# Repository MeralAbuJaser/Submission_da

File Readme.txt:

Student Name: Meral Abu-Jaser

Student #: 5003137888

Student Email: abujaser@unlv.nevada.edu

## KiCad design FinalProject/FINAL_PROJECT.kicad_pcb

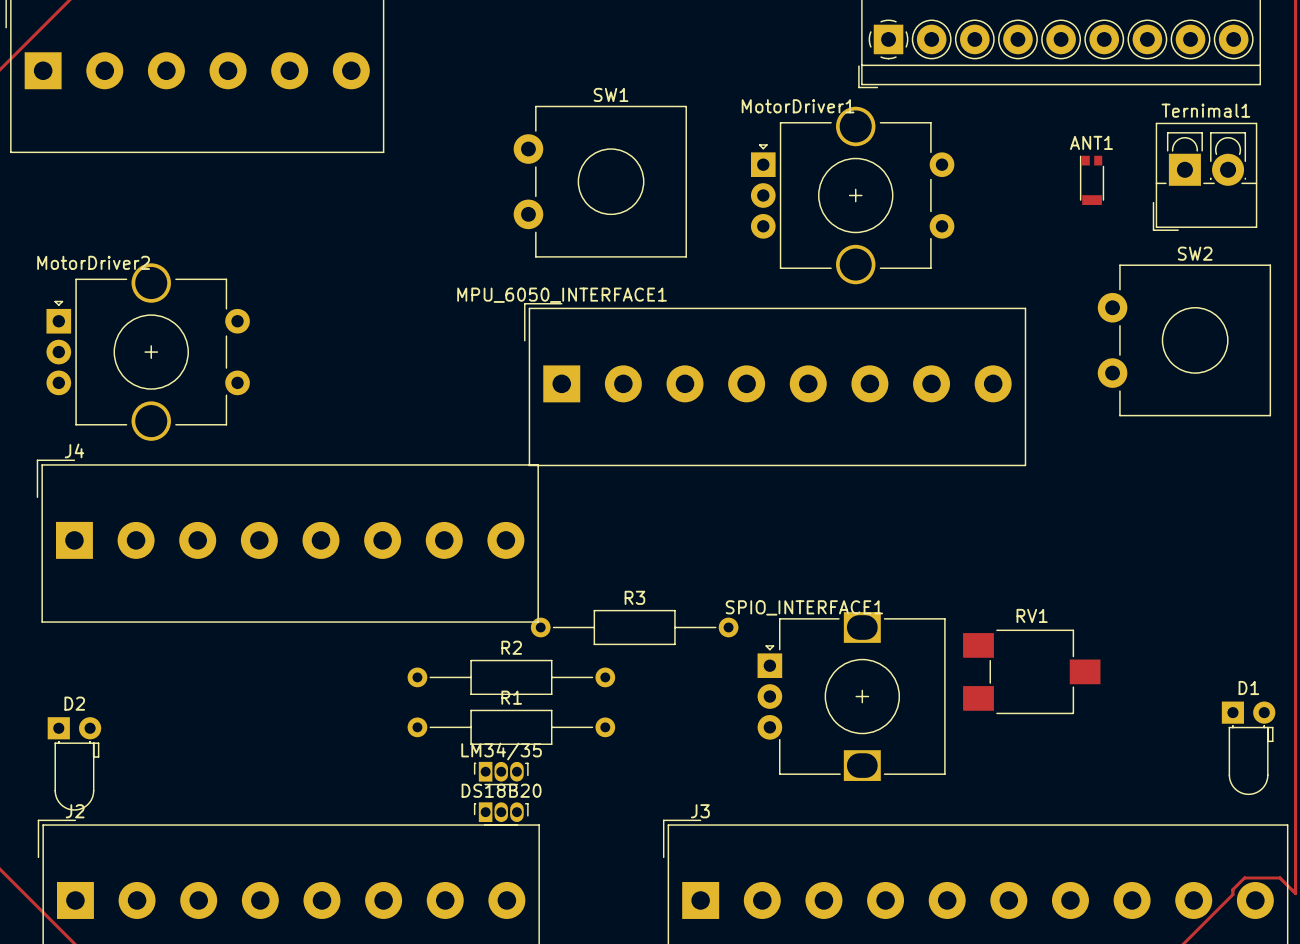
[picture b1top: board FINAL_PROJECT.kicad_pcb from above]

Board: 2 copper layers, 21 parts (0 on the bottom side), 18 nets.

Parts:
ANT1: Antenna_Shield; Pulse_W3011
D1, D2: LED_ALT; LED_D3.0mm_Horizontal_O1.27mm_Z2.0mm_Clear
DS18B20: Conn_01x03_Female; Diodes_SIP-3_4.1x1.5mm_P1.27mm
J1: Conn_01x06; Altech_AK300_1x06_P5.00mm_45-Degree
J2, J4: Conn_01x08; Altech_AK300_1x08_P5.00mm_45-Degree
J3: Conn_01x10; Altech_AK300_1x10_P5.00mm_45-Degree
LM34/35: Conn_01x03_Female; Diodes_SIP-3_4.1x1.5mm_P1.27mm
MPU_6050_INTERFACE1: MPU_6050_INTERFACE; Altech_AK300_1x08_P5.00mm_45-Degree
MotorDriver1, MotorDriver2: Conn_01x08_Female; RotaryEncoder_Alps_EC11E-Switch_Vertical_H20mm_CircularMoun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
R1, R2, R3: R_US; R_Axial_DIN0207_L6.3mm_D2.5mm_P15.24mm_Horizontal
RF1: RFM95W-915S2; TerminalBlock_4Ucon_1x09_P3.50mm_Horizontal
RV1: R_POT; Potentiometer_ACP_CA6-VSMD_Vertical
SPIO_INTERFACE1: Conn_01x14_Female; RotaryEncoder_Alps_EC12E_Vertical_H20mm
SW1, SW2: SW_Push; SW_CW_GPTS203211B
Ternimal1: Screw_Terminal_01x02; TerminalBlock_4Ucon_1x02_P3.50mm_Vertical

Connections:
+3V3: J2.3, MPU_6050_INTERFACE1.1
+5V: D1.1, D2.1, DS18B20.3, J2.4, LM34/35.1
/PB2: J3.8, RF1.5
/PB3: J3.7, RF1.3
/PB4: J3.6, RF1.2
/PB5: J3.5, RF1.4
/PC0: J1.1, RV1.3
/PC1: J1.2, LM34/35.2
/PC4: DS18B20.2, J1.5, J3.2
/PC5: J1.6, J3.1
/PD2: J4.6, SW2.2
/PD3: J4.5, SW1.2
/PD5: J4.3, R1.1, RF1.7
/PD6: J4.2, R2.1
GND: ANT1.2, DS18B20.1, J2.5, J2.6, J3.4, LM34/35.3, MPU_6050_INTERFACE1.2, R3.1, RF1.1, RF1.8, RV1.1, SW1.1, SW2.1
unnamed: ANT1.1, RF1.9
unnamed: D1.2, R1.2
unnamed: D2.2, R2.2

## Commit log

2020-02-20 Create DesignAssignments
2020-02-20 DesignAssignments
2020-03-04 Create Assignment 1B
2020-03-04 Create DA1B
2020-03-04 DA1B
2020-03-10 Create DA2A
2020-03-10 Update DA2A
2020-03-10 DA2A
2020-04-01 DA2B
2020-04-03 Create DA2B
2020-04-10 Create DA2C
2020-04-15 DA3A
2020-04-29 DA3B
2020-04-29 Create Assignments description
2020-04-29 Update Assignments description
2020-05-02 Midterm 1
2020-05-02 Create Assignment description
2020-05-02 Rename Midterm 1/Midterm1/Assignment description to Midterm description
2020-05-02 Create Mi
2020-05-02 Update Mi
2020-05-02 Create Midterm description
2020-05-08 DA4A
2020-05-08 CPE301D
2020-05-10 Midterm2
2020-05-11 DA4B
